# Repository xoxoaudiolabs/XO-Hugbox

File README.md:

# XO-Hugbox

**A pocket groovebox and MIDI controller from XOXO Audio Labs.**
16 mechanical pads, 4 knobs, a little OLED, a speaker and a headphone jack, running on a battery.
Play it on its own, or use it as a USB/Bluetooth MIDI companion for XOXO Studio and the FM-1 Companion Studio.

> **Status: prototype.** The hardware design is complete and the full firmware runs in the browser emulator, but no
> unit has been built yet. Expect changes once the first boards are assembled; see the [roadmap](#roadmap).

---

## What it does

- **Sampler:** 16 sample pads with pitch, decay, filter, level, pan and choke groups. A built-in kit is generated at boot; your recordings can go on any pad.
- **Sampling:** a built-in mic, one-handed. Shift + REC opens the sampler; tap or hold any pad to record (a beep counts you in), trim, fade, normalise or reverse it in the same sample editor as XOXO Studio, then tap the pad to save it to. Samples are kept on the flash.
- **Synth:** 6 voices, two oscillators (saw, square, sine, noise), 2-operator FM, a resonant filter with its own envelope, ADSR, analog-style drift and glide.
- **Chords and arpeggiator:** chords built from the scale (5th, triad, 7th, sus2, sus4, with inversions); the arp does up/down/up-down/random/as-played, 1/4 to 1/32 including triplets, 1–3 octaves, with latch.
- **Sequencer:** 16 steps × 4 pages = 64 steps, swing, live recording, and per-step velocity, pitch, gate and probability.
- **FX:** drive, bitcrush, sample-rate reduction, a tempo-synced ping-pong delay, and a low cut.
- **Modes:** Standalone, Controller (MIDI only) and Layered (both).
- **MIDI over USB and Bluetooth:** notes out and in, knob CCs in Controller mode, clock in or out, General MIDI drum notes.
- **Projects:** autosaves as you go, plus 8 save slots; copy/paste/clear sequencer pages, track mutes, tap tempo.

## Try it now: the emulator

Download or clone the repo and open **[`sim/index.html`](sim/index.html)** in Chrome or Edge (double-click it). It's
one self-contained file. Click **Power on**, then play the pads with the mouse or the keys `1234 / QWER / ASDF / ZXCV`;
Shift is the Shift key. The built-in **Hugbox guide** panel walks through everything, from "how do I turn on chords"
to MIDI sync, and your projects are saved in the browser.

The emulator runs **the same C++ as the device** (`firmware/lib/hugbox_core`), compiled to WebAssembly with the real
display driver, so the screen and the sound match the hardware. See [`sim/README.md`](sim/README.md).

## Controls

| Control | What it does |
|---|---|
| Pads | Play the sampler's 16 sounds, or synth notes in a scale (bottom-left = lowest). In SEQ, toggle steps. |
| Knobs | 4 parameters of the current page. Hold **Shift** for 4 more. Knobs "pick up" a value only once turned past it. |
| Shift + pad | Top row: PLAY · SEQ · SOUND · FX. Row 2: seq page 1–4. Row 3: SAMPLER · SYNTH · run/stop · rec (hold 1 s: record a sample). Bottom row: Standalone · Controller · Layered · Settings. |
| Double-tap Shift | Shows the shortcut map; tap a pad to jump there. |
| Hold a step + knob | Set that step's velocity, pitch, gate or probability. |
| SETTINGS pads | Tap S1–S8 to load, hold to save · copy/paste/clear page · mutes · tap tempo · MIDI panic. |

## Build one

Open the interactive 3D build guide, **[`docs/build-guide/index.html`](docs/build-guide/index.html)**. It shows every part
in place, explodes the model, and walks through the assembly in 13 steps with orientation, jumper and polarity notes.
It needs an internet connection to load three.js.

**Main parts:** Seeed XIAO ESP32-S3 · PCF8574T I/O expander · MAX98357A amp + 3 W speaker · PCM5102A DAC (headphone/line out) ·
1.3" SH1106 OLED · 4× B10K pots · 17× MX switches + 16× 1N4148 · 1100 mAh LiPo · 2-layer PCB · 3D-printed plate and shell.
About $60-85 in parts per unit at small quantities (rough estimate). Full parts list, costs, what to measure before ordering, PCB order notes and printing settings:
**[docs/hardware.md](docs/hardware.md)**.

## Repository layout

```
hardware/
  layout.py              single source of truth for every position and dimension
  pcb/                   KiCad 7 scripts, routed boards, gerbers
                         v1: xo_hugbox_gerbers.zip (order candidate)
                         v1.1: separate speaker data line (pending a breadboard test)
  mechanical/            plate + shell generators, STLs, assembly scene
firmware/
  lib/hugbox_core/       the instrument: UI, sequencer, chords/arp, synth, sampler, FX (shared with the emulator)
  src/hugbox/            board layer (inputs, OLED, I2S, flash, MIDI)    -> pio run -e hugbox
  src/bringup/           hardware bring-up test                          -> pio run -e bringup
  src/duali2s/           v1.1 speaker-line breadboard test               -> pio run -e duali2s
sim/                     browser emulator (WASM build of hugbox_core)
docs/
  build-guide/           interactive 3D build guide
  hardware.md            parts, ordering, printing, assembly, regenerating the design files
  firmware.md            firmware architecture, controls, projects, MIDI
  speaker-path-plan.md   board v1.1 plan and test checklist
  images/                renders and screen images
```

## Building from source

- **Firmware** (PlatformIO, Arduino-ESP32 core 3.x via pioarduino): `cd firmware && pio run -e hugbox -t upload`, then
  `pio device monitor`. Flash `-e bringup` first on a new board. Details: [docs/firmware.md](docs/firmware.md).
- **Emulator:** after changing `firmware/lib/hugbox_core`, run `sim/build_wasm.sh` (emscripten, Linux/WSL).
  See [`sim/README.md`](sim/README.md).
- **Hardware:** KiCad 7 Python scripts + Freerouting + OpenSCAD, all driven by `hardware/layout.py`.
  See [docs/hardware.md](docs/hardware.md#regenerating-the-hardware-files).

## Roadmap

1. ✅ UI: views, knob pages, shift layer, sequencer grid, modes
2. ✅ Synth + sample engine
3. ✅ Projects + sequencer extras
4. ✅ FX
5. ✅ USB + BLE MIDI
6. ⬜ Bring-up on real hardware, then order the PCB (v1 or v1.1)
7. ✅ Mic sampling + user samples on flash (in code and the emulator; not on hardware yet)

## Contributing

Issues and pull requests are welcome, especially build reports once you've assembled one. Keep `hardware/layout.py`
as the single source of truth, never hand-edit generated files, and rebuild both the firmware and the emulator when you
change `firmware/lib/hugbox_core` so they stay identical. [CLAUDE.md](CLAUDE.md) has the short version of the house rules.

## License

- **Hardware** (`hardware/`): [CERN-OHL-S-2.0](LICENSES/CERN-OHL-S-2.0.txt)
- **Software** (`firmware/`, `sim/`, build-guide code): [MIT](LICENSES/MIT.txt)
- **Docs and images:** [CC BY-SA 4.0](LICENSES/CC-BY-SA-4.0.txt)

See [LICENSE](LICENSE) for the details and [NOTICE.md](NOTICE.md) for third-party components.
© 2026 XOXO Audio Labs LLC.

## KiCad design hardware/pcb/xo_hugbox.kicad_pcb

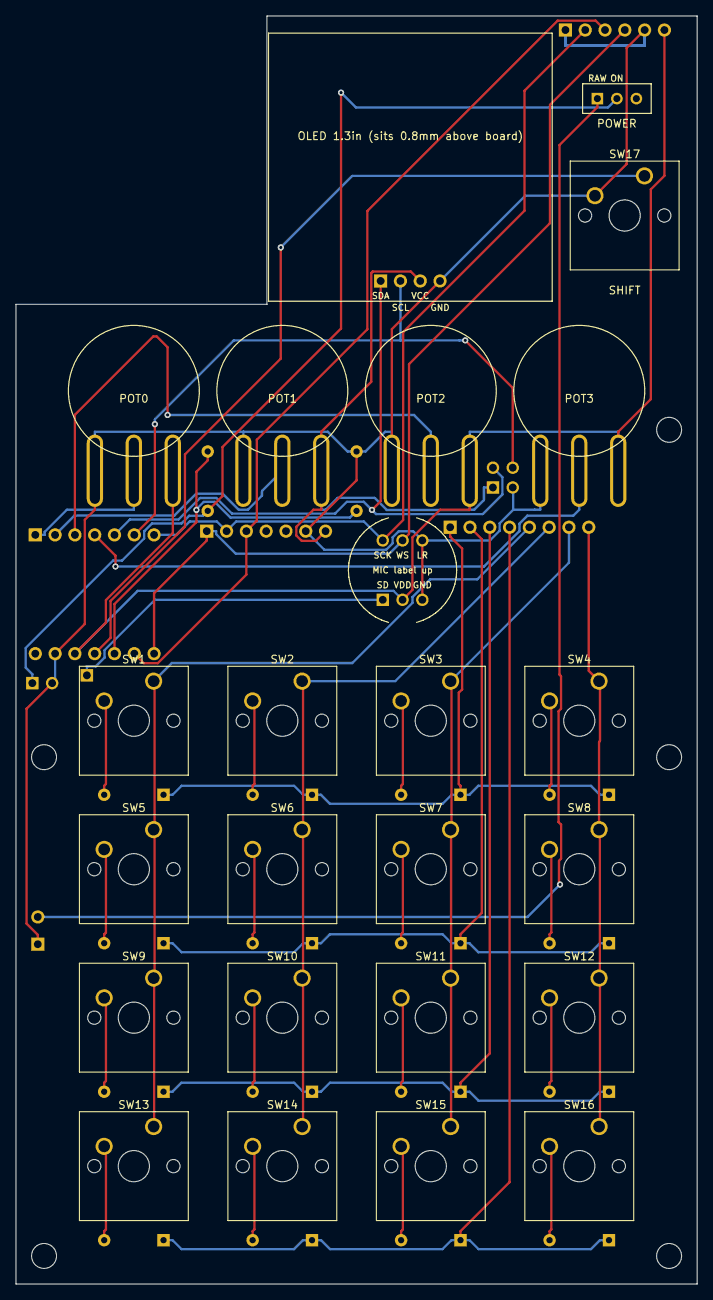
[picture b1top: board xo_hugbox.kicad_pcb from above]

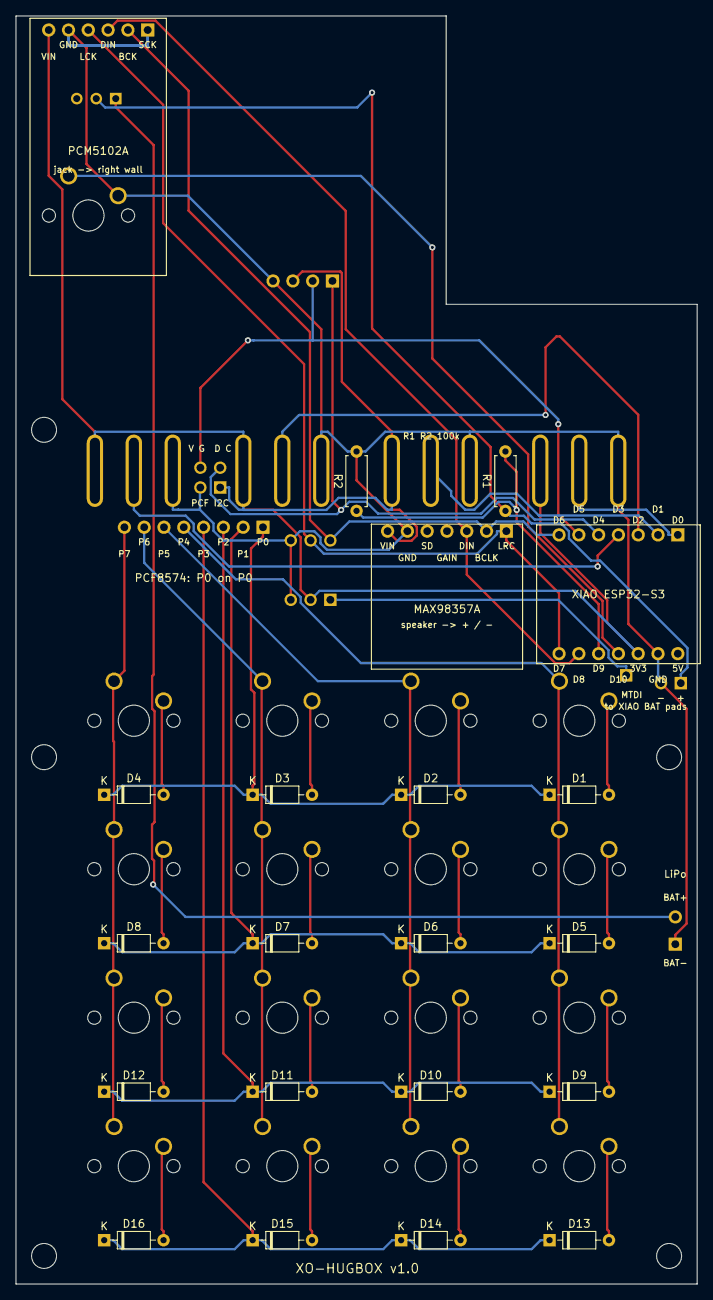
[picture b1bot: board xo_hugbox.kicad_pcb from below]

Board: 2 copper layers, 87.4 x 162.7 mm, 55 parts (18 on the bottom side), 40 nets.

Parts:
D1, D2, D3, D4, D5, D6, D7, D8, D9, D10, D11, D12, D13, D14, D15, D16: D_DO-35_SOD27_P7.62mm_Horizontal
H1, H2, H3, H4, H5: MountingHole_3.2mm_M3
J9: J9
J11: J11
J13: J13
J_MIC: J_MIC
J_MTDI: J_MTDI
R1, R2: R_Axial_DIN0207_L6.3mm_D2.5mm_P7.62mm_Horizontal
RV1: RV1
RV2: RV2
RV3: RV3
RV4: RV4
SW1, SW2, SW3, SW4, SW5, SW6, SW7, SW8, SW9, SW10, SW11, SW12, SW13, SW14, SW15, SW16, SW17: SW_Cherry_MX_1.00u_PCB
SW18: SW18
U1: U1
U2: U2
U3: U3
U4: U4
U5: U5

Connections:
3V3: J9.1, J_MIC.2, RV1.3, RV2.3, RV3.3, RV4.3, U1.10, U3.7, U4.6, U5.3
BAT_RAW: J11.2, SW18.1
BAT_SW: J13.1, R1.1, SW18.2
BCK: J_MIC.4, U1.7, U3.2, U4.2
C0: SW1.1, SW5.1, SW9.1, SW13.1, U2.5
C1: SW2.1, SW6.1, SW10.1, SW14.1, U2.6
C2: SW3.1, SW7.1, SW11.1, SW15.1, U2.7
C3: SW4.1, SW8.1, SW12.1, SW16.1, U2.8
DIN: U1.13, U3.3, U4.3
GND: J9.2, J11.1, J13.2, J_MIC.3, J_MIC.6, R2.2, RV1.1, RV2.1, RV3.1, RV4.1, SW17.2, U1.9, U3.6, U4.1, U4.5, U5.4
LRCK: J_MIC.5, U1.14, U3.1, U4.4
MIC_SD: J_MIC.1, J_MTDI.1
POT0: RV1.2, U1.1
POT1: RV2.2, U1.2
POT2: RV3.2, U1.3
POT3: RV4.2, U1.4
R0: D1.1, D2.1, D3.1, D4.1, U2.1
R1: D5.1, D6.1, D7.1, D8.1, U2.2
R2: D9.1, D10.1, D11.1, D12.1, U2.3
R3: D13.1, D14.1, D15.1, D16.1, U2.4
SCL: J9.4, U1.6, U5.2
SDA: J9.3, U1.5, U5.1
SHIFT: SW17.1, U1.11
SWD1: D1.2, SW1.2
SWD2: D2.2, SW2.2
SWD3: D3.2, SW3.2
SWD4: D4.2, SW4.2
SWD5: D5.2, SW5.2
SWD6: D6.2, SW6.2
SWD7: D7.2, SW7.2
SWD8: D8.2, SW8.2
SWD9: D9.2, SW9.2
SWD10: D10.2, SW10.2
SWD11: D11.2, SW11.2
SWD12: D12.2, SW12.2
SWD13: D13.2, SW13.2
SWD14: D14.2, SW14.2
SWD15: D15.2, SW15.2
SWD16: D16.2, SW16.2
VSENSE: R1.2, R2.1, U1.12

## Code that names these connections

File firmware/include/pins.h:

// XO-Hugbox - pin map for the v1 board (Seeed XIAO ESP32-S3)
#pragma once

// Pots (WH148 10k, wiper on ADC1). Wired so clockwise = higher reading.
#define PIN_POT0   D0
#define PIN_POT1   D1
#define PIN_POT2   D2
#define PIN_POT3   D3

// I2C bus: OLED (SH1106 1.3", 0x3C) + PCF8574T key-matrix expander (0x20-0x27, set by A0-A2 bridges)
#define PIN_SDA    D4
#define PIN_SCL    D5
#define OLED_ADDR      0x3C
#define PCF8574_ADDR   0x20   // confirm with an I2C scan
// OLED header faces the knobs, so the screen is mounted upside down: use U8G2_R2.

// I2S out -> MAX98357A (speaker) and PCM5102A (line out) in parallel
#define PIN_I2S_BCK   D6
#define PIN_I2S_LRCK  D7
#define PIN_I2S_DOUT  D8
// INMP441 mic data: the XIAO's MTDI pad (GPIO41, underside) -> wire -> J_MTDI -> J_MIC SD. Not a header pin.
#define PIN_I2S_DIN   41

// Battery voltage: 100k/100k divider from the switched battery rail (Vbat = reading x 2)
#define PIN_VBAT_SENSE D9

// Shift key: MX switch to GND, use INPUT_PULLUP, active low
#define PIN_SHIFT  D10

// PCF8574 key matrix (16 pads). Diode per key, anode at switch, cathode to row.
// Scan: drive one row LOW (others high), read columns (PCF quasi-bidirectional = weak pull-up),
// a pressed key pulls its column LOW.
// P0..P3 = rows R0..R3 (R0 = top row, nearest the knobs)
// P4..P7 = columns C0..C3 (C0 = left)
#define PCF_ROW_MASK 0x0F
#define PCF_COL_MASK 0xF0

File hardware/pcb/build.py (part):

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for a,c in [((_x1,L.PCM_ROW_Y),(_x1,_gy)),((_x1,_gy),(_x5,_gy)),((_x5,_gy),(_x5,L.PCM_ROW_Y))]:
    t=pcbnew.PCB_TRACK(board); t.SetStart(K(*a)); t.SetEnd(K(*c)); t.SetWidth(mm(0.3)); t.SetLayer(pcbnew.B_Cu); t.SetNet(net("GND")); board.Add(t)
# ---- battery + divider ----
custom("J11",[("BAT-",5.2,46,"GND"),("BAT+",5.2,49.5,"BAT_RAW")],lab_dy=0,labels=False)
text("BAT-",5.2,43.6,0.8); text("BAT+",5.2,52.0,0.8); text("LiPo",5.2,55,0.9)
custom("J13",[("+",4.5,79.5,"BAT_SW"),("-",7.04,79.5,"GND")],size=1.6,lab_dy=-1.9)
text("to XIAO BAT pads",9,76.5,0.8)
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# SD VDD GND row toward the keys (only one way round matches). SD runs to J_MTDI by the XIAO, where a wire from the
# XIAO's MTDI pad (GPIO41, on its underside) lands.
mcx,mcy=L.MIC_C; mp,mdy=L.MIC_PITCH,L.MIC_ROW_DY
mic_pins=[("SD",-1,-1,"MIC_SD"),("VDD",0,-1,"3V3"),("GND",1,-1,"GND"),("SCK",-1,1,"BCK"),("WS",0,1,"LRCK"),("LR",1,1,"GND")]
custom("J_MIC",[(n,mcx+mp*i,mcy+mdy*j,nn) for (n,i,j,nn) in mic_pins],size=1.6,labels=False)
for (n,i,j,_) in mic_pins: text(n,mcx+mp*i,mcy+mdy*j-1.9*j,0.7,back=False)   # labels between the rows, like the module
_mr=L.MIC_D/2
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    if abs(math.sin((a0+a1)/2))>0.97: continue                                 # leave the notch ends open
    seg((mcx+_mr*math.cos(a0),mcy+_mr*math.sin(a0)),(mcx+_mr*math.cos(a1),mcy+_mr*math.sin(a1)),pcbnew.F_SilkS,0.15)
text("MIC label up",mcx,mcy,0.7,back=False)
custom("J_MTDI",[("",L.MTDI_PAD[0],L.MTDI_PAD[1],"MIC_SD")],size=1.6,labels=False)
text("MTDI",L.MTDI_PAD[0]-0.7,L.MTDI_PAD[1]-2.5,0.8)
text("XO-HUGBOX v1.1" if V11 else "XO-HUGBOX v1.0",46,4.4,1.2)
board.BuildConnectivity()
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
